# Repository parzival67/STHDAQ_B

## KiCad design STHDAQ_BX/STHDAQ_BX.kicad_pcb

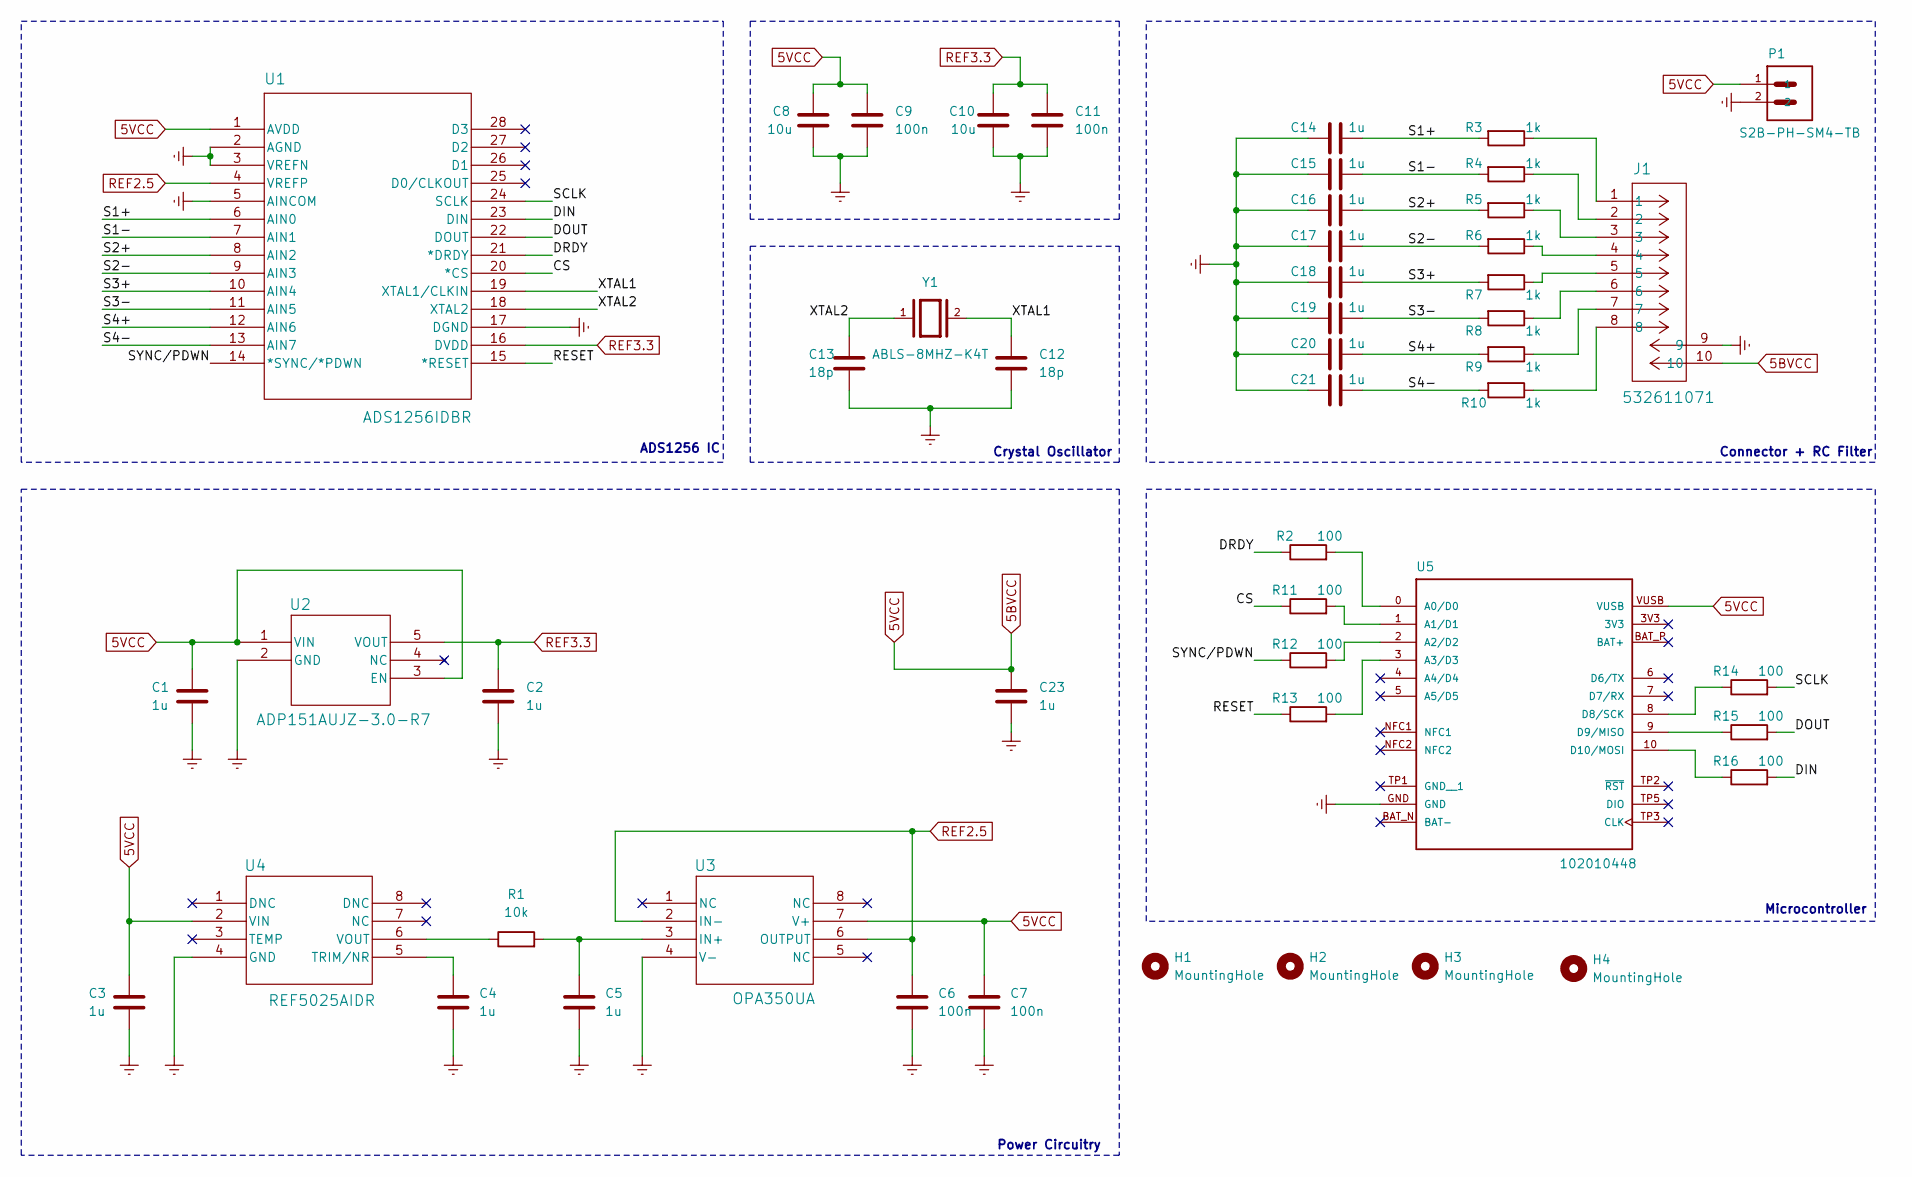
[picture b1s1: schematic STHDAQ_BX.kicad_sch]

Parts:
C1, C2, C3, C4, C5, C14, C15, C16, C17, C18, C19, C20, C21, C23: 1u; C_0603_1608Metric_Pad1.08x0.95mm_HandSolder
C6, C7, C9, C11: 100n; C_0603_1608Metric_Pad1.08x0.95mm_HandSolder
C8, C10: 10u; C_0603_1608Metric_Pad1.08x0.95mm_HandSolder
C12, C13: 18p; C_0603_1608Metric_Pad1.08x0.95mm_HandSolder
H1, H2, H3, H4: MountingHole; MountingHole_3.2mm_M3_ISO14580_Pad_TopBottom
J1: 532611071; CONN_532610001
P1: S2B-PH-SM4-TB; JST_S2B-PH-SM4-TB
R1: 10k; R_0603_1608Metric_Pad0.98x0.95mm_HandSolder
R2, R11, R12, R13, R14, R15, R16: 100; R_0603_1608Metric_Pad0.98x0.95mm_HandSolder
R3, R4, R5, R6, R7, R8, R9, R10: 1k; R_0603_1608Metric_Pad0.98x0.95mm_HandSolder
U1: ADS1256IDBR
U2: ADP151AUJZ-3.0-R7; ADP151AUJZ-3P0-R7
U3: OPA350UA
U4: REF5025AIDR
U5: 102010448; PARTREV 2022/08/18
Y1: ABLS-8MHZ-K4T; XTAL_ABLS-8.000MHZ-K4T; PARTREV 02.16.2021

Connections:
5BVCC: C1.2, C3.2, C7.2, C8.2, C9.2, C23.2, J1.10, P1.1, U1.1 (AVDD), U2.1 (VIN), U2.3 (EN), U3.7 (V+), U4.2 (VIN), U5.VUSB
/CS: R11.1, U1.20 (*CS)
/DIN: R16.2, U1.23 (DIN)
/DOUT: R15.2, U1.22 (DOUT)
/DRDY: R2.1, U1.21 (*DRDY)
/RESET: R13.1, U1.15 (*RESET)
/S1+: C14.1, R3.2, U1.6 (AIN0)
/S1-: C15.1, R4.2, U1.7 (AIN1)
/S2+: C16.1, R5.2, U1.8 (AIN2)
/S2-: C17.1, R6.2, U1.9 (AIN3)
/S3+: C18.1, R7.2, U1.10 (AIN4)
/S3-: C19.1, R8.2, U1.11 (AIN5)
/S4+: C20.1, R9.2, U1.12 (AIN6)
/S4-: C21.1, R10.2, U1.13 (AIN7)
/SCLK: R14.2, U1.24 (SCLK)
/SYNC/PDWN: R12.1, U1.14 (*SYNC/*PDWN)
/XTAL1: C12.2, U1.19 (XTAL1/CLKIN), Y1.2
/XTAL2: C13.2, U1.18 (XTAL2), Y1.1
Earth: C1.1, C2.1, C3.1, C4.1, C5.1, C6.1, C7.1, C8.1, C9.1, C10.1, C11.1, C12.1, C13.1, C14.2, C15.2, C16.2, C17.2, C18.2, C19.2, C20.2, C21.2, C23.1, J1.9, P1.2, U1.2 (AGND), U1.3 (VREFN), U1.5 (AINCOM), U1.17 (DGND), U2.2 (GND), U3.4 (V-), U4.4 (GND), U5.GND
unnamed: J1.1, R3.1
unnamed: J1.2, R4.1
unnamed: J1.3, R5.1
unnamed: J1.4, R6.1
unnamed: J1.5, R7.1
unnamed: J1.6, R8.1
unnamed: J1.7, R9.1
unnamed: J1.8, R10.1
unnamed: C5.2, R1.2, U3.3 (IN+)
unnamed: C4.2, U4.5 (TRIM/NR)
unnamed: R1.1, U4.6 (VOUT)
unnamed: R2.2, U5.0 (A0/D0)
unnamed: R11.2, U5.1 (A1/D1)
unnamed: R12.2, U5.2 (A2/D2)
unnamed: R13.2, U5.3 (A3/D3)
unnamed: R14.1, U5.8 (D8/SCK)
unnamed: R15.1, U5.9 (D9/MISO)
unnamed: R16.1, U5.10 (D10/MOSI)
REF2.5: C6.2, U1.4 (VREFP), U3.2 (IN-), U3.6 (OUTPUT)
REF3.3: C2.2, C10.2, C11.2, U1.16 (DVDD), U2.5 (VOUT)

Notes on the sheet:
Connector + RC Filter
Microcontroller
Power Circuitry
ADS1256 IC
Crystal Oscillator

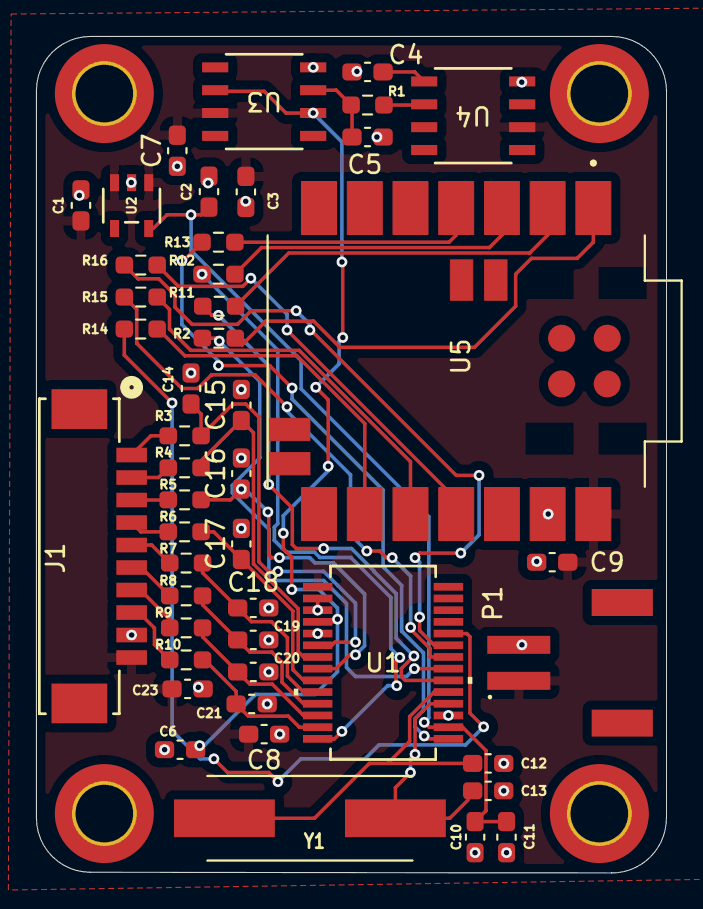
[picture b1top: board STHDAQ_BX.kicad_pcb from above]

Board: 2 copper layers, 35.0 x 46.5 mm, 50 parts (0 on the bottom side), 39 nets.

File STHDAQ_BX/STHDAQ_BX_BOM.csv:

"Reference","Qty","Value","Datasheet","Footprint","DNP","#","MANUFACTURER","Package","Description"
"P1","1","S2B-PH-SM4-TB","","daFootprintsBX:JST_S2B-PH-SM4-TB","","1","JST","None",""
"U4","1","REF5025AIDR","REF5025AIDR","daFootprints:REF5025AIDR","","2","","",""
"U3","1","OPA350UA","OPA350UA","daFootprints:OPA350UA","","3","","",""
"U1","1","ADS1256IDBR","ADS1256IDBR","daFootprints:ADS1256IDBR","","4","","",""
"U2","1","ADP151AUJZ-3.0-R7","ADP151AUJZ-3.0-R7","daFootprints:ADP151AUJZ-3P0-R7","","5","","",""
"Y1","1","ABLS-8MHZ-K4T","","daFootprints:XTAL_ABLS-8.000MHZ-K4T","","6","Abracon","HC-49/US Abracon LLC",""
"J1","1","532611071","532611071","daFootprints:CONN_532610001","","7","","",""
"U5","1","102010448","","daFootprints:102010448","","8","Seeed Technology Co., Ltd","None",""
"R1","1","10k","~","Resistor_SMD:R_0603_1608Metric_Pad0.98x0.95mm_HandSolder","","9","","","Resistor"
"R3,R4,R5,R6,R7,R8,R9,R10","8","1k","~","Resistor_SMD:R_0603_1608Metric_Pad0.98x0.95mm_HandSolder","","10","","","Resistor"
"R2,R11,R12,R13,R14,R15,R16","7","100","~","Resistor_SMD:R_0603_1608Metric_Pad0.98x0.95mm_HandSolder","","11","","","Resistor"
"C8,C10","2","10u","~","Capacitor_SMD:C_0603_1608Metric_Pad1.08x0.95mm_HandSolder","","12","","","Unpolarized capacitor"
"C1,C2,C3,C4,C5,C14,C15,C16,C17,C18,C19,C20,C21,C23","14","1u","~","Capacitor_SMD:C_0603_1608Metric_Pad1.08x0.95mm_HandSolder","","13","","","Unpolarized capacitor"
"C6,C7,C9,C11","4","100n","~","Capacitor_SMD:C_0603_1608Metric_Pad1.08x0.95mm_HandSolder","","14","","","Unpolarized capacitor"
"C12,C13","2","18p","~","Capacitor_SMD:C_0603_1608Metric_Pad1.08x0.95mm_HandSolder","","15","","","Unpolarized capacitor"

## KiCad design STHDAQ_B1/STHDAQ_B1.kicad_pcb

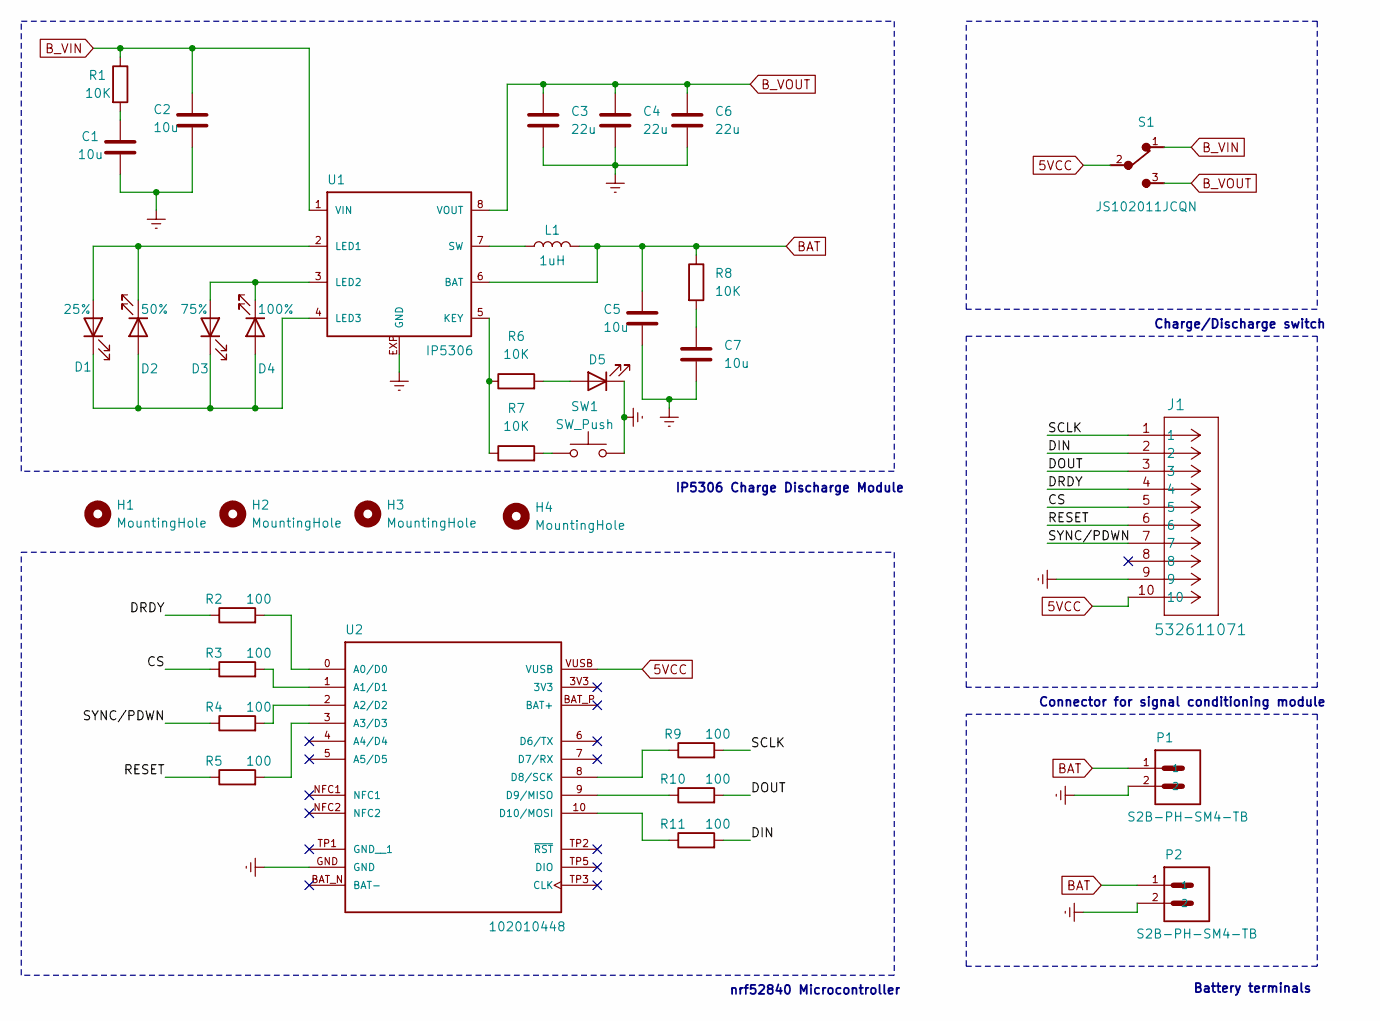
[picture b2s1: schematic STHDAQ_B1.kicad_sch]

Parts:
C1, C2, C5, C7: 10u; C_0603_1608Metric_Pad1.08x0.95mm_HandSolder
C3, C4, C6: 22u; C_0603_1608Metric_Pad1.08x0.95mm_HandSolder
D1: 25%; LED_0603_1608Metric_Pad1.05x0.95mm_HandSolder
D2: 50%; LED_0603_1608Metric_Pad1.05x0.95mm_HandSolder
D3: 75%; LED_0603_1608Metric_Pad1.05x0.95mm_HandSolder
D4: 100%; LED_0603_1608Metric_Pad1.05x0.95mm_HandSolder
D5: LED; LED_0603_1608Metric_Pad1.05x0.95mm_HandSolder
H1, H2, H3, H4: MountingHole; MountingHole_3.2mm_M3_ISO14580_Pad_TopBottom
J1: 532611071; CONN_532610001
L1: 1uH; L_0603_1608Metric_Pad1.05x0.95mm_HandSolder
P1, P2: S2B-PH-SM4-TB; JST_S2B-PH-SM4-TB
R1, R6, R7, R8: 10K; R_0603_1608Metric_Pad0.98x0.95mm_HandSolder
R2, R3, R4, R5, R9, R10, R11: 100; R_0603_1608Metric_Pad0.98x0.95mm_HandSolder
S1: JS102011JCQN; SW_JS102011JCQN; PARTREV 29 JUN 2016
SW1: SW_Push; Panasonic_EVQPUJ_EVQPUA
U1: IP5306
U2: 102010448; PARTREV 2022/08/18

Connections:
5VCC: J1.10, S1.2, U2.VUSB
/CS: J1.5, R3.1
/DIN: J1.2, R11.2
/DOUT: J1.3, R10.2
/DRDY: J1.4, R2.1
/RESET: J1.6, R5.1
/SCLK: J1.1, R9.2
/SYNC/PDWN: J1.7, R4.1
BAT: C5.1, L1.2, P1.1, P2.1, R8.1, U1.6 (BAT)
B_VIN: C2.1, R1.1, S1.1, U1.1 (VIN)
B_VOUT: C3.1, C4.1, C6.1, S1.3, U1.8 (VOUT)
Earth: C1.2, C2.2, C3.2, C4.2, C5.2, C6.2, C7.2, D5.1 (K), J1.9, P1.2, P2.2, SW1.2, U1.EXP (GND), U2.GND
unnamed: C1.1, R1.2
unnamed: C7.1, R8.2
unnamed: D1.2 (A), D2.1 (K), U1.2 (LED1)
unnamed: D1.1 (K), D2.2 (A), D3.1 (K), D4.2 (A), U1.4 (LED3)
unnamed: D3.2 (A), D4.1 (K), U1.3 (LED2)
unnamed: D5.2 (A), R6.2
unnamed: R7.2, SW1.1
unnamed: R6.1, R7.1, U1.5 (KEY)
unnamed: L1.1, U1.7 (SW)
unnamed: R2.2, U2.0 (A0/D0)
unnamed: R3.2, U2.1 (A1/D1)
unnamed: R4.2, U2.2 (A2/D2)
unnamed: R5.2, U2.3 (A3/D3)
unnamed: R9.1, U2.8 (D8/SCK)
unnamed: R10.1, U2.9 (D9/MISO)
unnamed: R11.1, U2.10 (D10/MOSI)

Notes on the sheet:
nrf52840 Microcontroller
Connector for signal conditioning module
Battery terminals
IP5306 Charge Discharge Module
Charge/Discharge switch

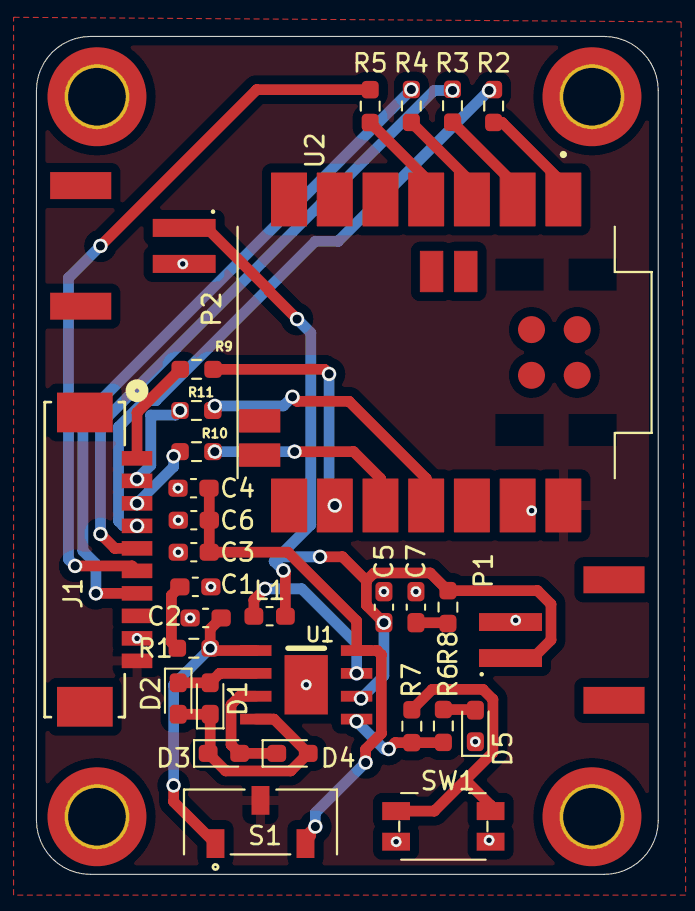
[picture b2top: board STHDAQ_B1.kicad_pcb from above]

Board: 2 copper layers, 34.5 x 46.6 mm, 35 parts (0 on the bottom side), 28 nets.

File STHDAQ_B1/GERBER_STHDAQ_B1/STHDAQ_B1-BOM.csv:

#,Reference,Qty,MANUFACTURER,Manufacturer Part Number,Value,Package,Type
1,"P1,P2",2,JST Sales America Inc.,S2B-PH-SM4-TB,-,,SMD
2,S1,1,CK COMPONENTS,JS102011JCQN,-,,SMD
3,U1,1,,IP5306,-,,SMD
4,J1,1,Molex,532611071,-,S2B-PH-SM4-TB,SMD
5,"C1,C2,C5,C7",4,,,10u,0603,SMD
6,"C3,C4,C6",3,,,22u,0603,SMD
7,D1,1,,LED,25%,0603,SMD
8,D2,1,,LED,50%,0603,SMD
9,D3,1,,LED,75%,0603,SMD
10,D4,1,,LED,100%,0603,SMD
11,D5,1,,LED,LED,0603,SMD
12,L1,1,,,1uH,0603,SMD
13,"R1,R6,R7,R8",4,,,10K,0603,SMD
14,"R2,R3,R4,R5,R9,R10,R11",7,,,100,0603,SMD
15,SW1,1,,,SW_Push,,SMD

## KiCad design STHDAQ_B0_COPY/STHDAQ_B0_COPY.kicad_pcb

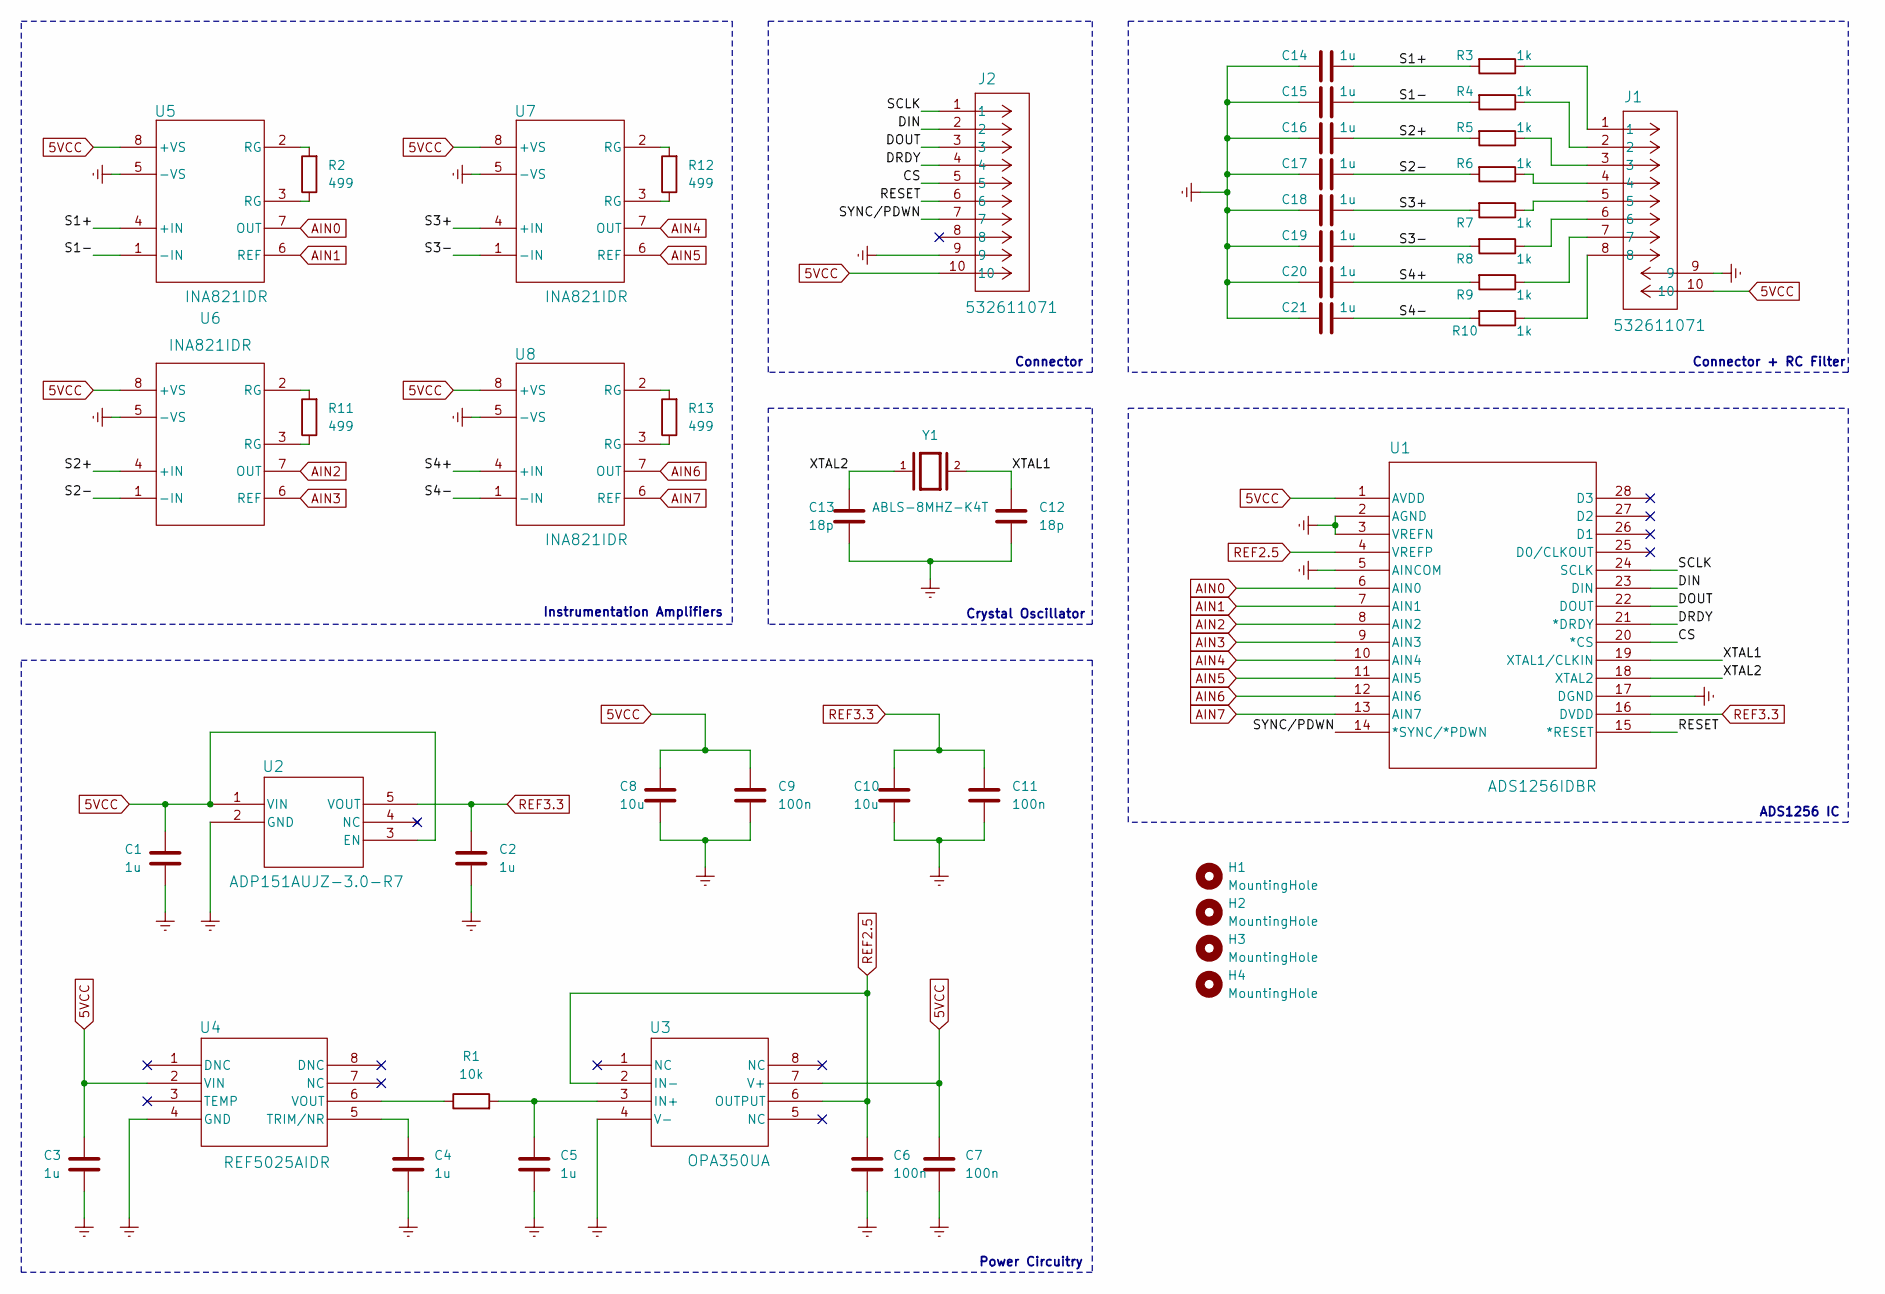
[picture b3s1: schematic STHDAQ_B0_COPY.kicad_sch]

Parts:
C1, C2, C3, C4, C5, C14, C15, C16, C17, C18, C19, C20, C21: 1u; C_0201_0603Metric
C6, C7, C9, C11: 100n; C_0201_0603Metric
C8, C10: 10u; C_0201_0603Metric
C12, C13: 18p; C_0201_0603Metric
H1, H2, H3, H4: MountingHole; MountingHole_3.2mm_M3_ISO14580_Pad_TopBottom
J1, J2: 532611071; Molex_CLIK-Mate_502382-1070_1x10-1MP_P1.25mm_Vertical
R1: 10k; R_0201_0603Metric
R2, R11, R12, R13: 499; R_0201_0603Metric
R3, R4, R5, R6, R7, R8, R9, R10: 1k; R_0201_0603Metric
U1: ADS1256IDBR
U2: ADP151AUJZ-3.0-R7; ADP151AUJZ-3P0-R7
U3: OPA350UA
U4: REF5025AIDR
U5, U6, U7, U8: INA821IDR
Y1: ABLS-8MHZ-K4T; XTAL_ABLS-8.000MHZ-K4T; PARTREV 02.16.2021

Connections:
5VCC: C1.2, C3.2, C7.2, C8.2, C9.2, J1.10, J2.10, U1.1 (AVDD), U2.1 (VIN), U2.3 (EN), U3.7 (V+), U4.2 (VIN), U5.8 (+VS), U6.8 (+VS), U7.8 (+VS), U8.8 (+VS)
/CS: J2.5, U1.20 (*CS)
/DIN: J2.2, U1.23 (DIN)
/DOUT: J2.3, U1.22 (DOUT)
/DRDY: J2.4, U1.21 (*DRDY)
/RESET: J2.6, U1.15 (*RESET)
/S1+: C14.1, R3.2, U5.4 (+IN)
/S1-: C15.1, R4.2, U5.1 (-IN)
/S2+: C16.1, R5.2, U6.4 (+IN)
/S2-: C17.1, R6.2, U6.1 (-IN)
/S3+: C18.1, R7.2, U7.4 (+IN)
/S3-: C19.1, R8.2, U7.1 (-IN)
/S4+: C20.1, R9.2, U8.4 (+IN)
/S4-: C21.1, R10.2, U8.1 (-IN)
/SCLK: J2.1, U1.24 (SCLK)
/SYNC/PDWN: J2.7, U1.14 (*SYNC/*PDWN)
/XTAL1: C12.2, U1.19 (XTAL1/CLKIN), Y1.2
/XTAL2: C13.2, U1.18 (XTAL2), Y1.1
AIN0: U1.6 (AIN0), U5.7 (OUT)
AIN1: U1.7 (AIN1), U5.6 (REF)
AIN2: U1.8 (AIN2), U6.7 (OUT)
AIN3: U1.9 (AIN3), U6.6 (REF)
AIN4: U1.10 (AIN4), U7.7 (OUT)
AIN5: U1.11 (AIN5), U7.6 (REF)
AIN6: U1.12 (AIN6), U8.7 (OUT)
AIN7: U1.13 (AIN7), U8.6 (REF)
Earth: C1.1, C2.1, C3.1, C4.1, C5.1, C6.1, C7.1, C8.1, C9.1, C10.1, C11.1, C12.1, C13.1, C14.2, C15.2, C16.2, C17.2, C18.2, C19.2, C20.2, C21.2, J1.9, J2.9, U1.2 (AGND), U1.3 (VREFN), U1.5 (AINCOM), U1.17 (DGND), U2.2 (GND), U3.4 (V-), U4.4 (GND), U5.5 (-VS), U6.5 (-VS), U7.5 (-VS), U8.5 (-VS)
unnamed: J1.1, R3.1
unnamed: J1.2, R4.1
unnamed: J1.3, R5.1
unnamed: J1.4, R6.1
unnamed: J1.5, R7.1
unnamed: J1.6, R8.1
unnamed: J1.7, R9.1
unnamed: J1.8, R10.1
unnamed: R2.1, U5.3 (RG)
unnamed: R2.2, U5.2 (RG)
unnamed: R11.1, U6.3 (RG)
unnamed: R11.2, U6.2 (RG)
unnamed: R12.1, U7.3 (RG)
unnamed: R12.2, U7.2 (RG)
unnamed: R13.1, U8.3 (RG)
unnamed: R13.2, U8.2 (RG)
unnamed: C5.2, R1.2, U3.3 (IN+)
unnamed: C4.2, U4.5 (TRIM/NR)
unnamed: R1.1, U4.6 (VOUT)
REF2.5: C6.2, U1.4 (VREFP), U3.2 (IN-), U3.6 (OUTPUT)
REF3.3: C2.2, C10.2, C11.2, U1.16 (DVDD), U2.5 (VOUT)

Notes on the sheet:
Instrumentation Amplifiers
Connector + RC Filter
Connector
Power Circuitry
ADS1256 IC
Crystal Oscillator

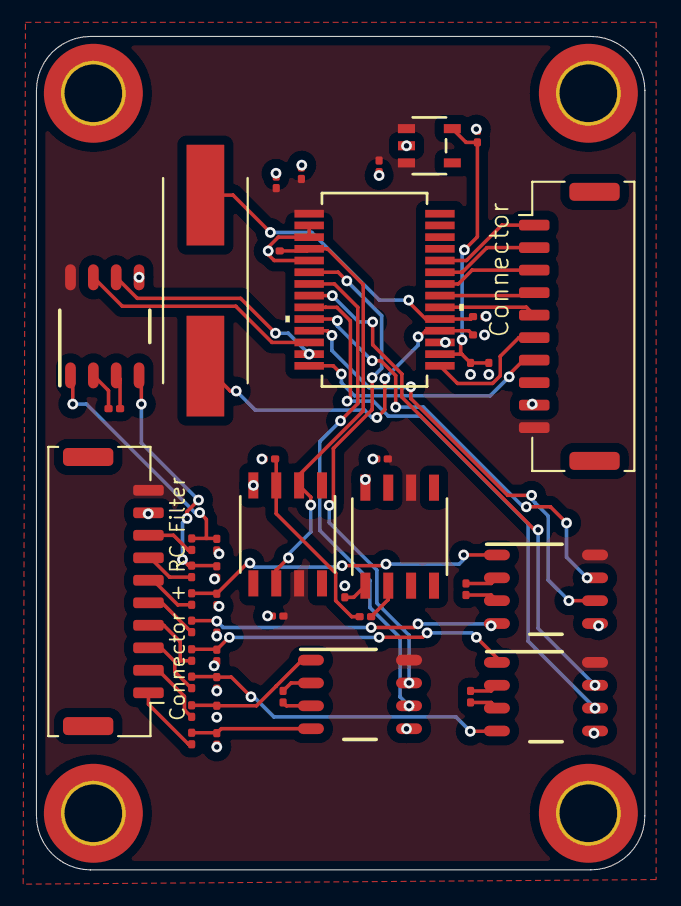
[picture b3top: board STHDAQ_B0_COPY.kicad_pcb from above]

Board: 2 copper layers, 33.8 x 46.3 mm, 49 parts (0 on the bottom side), 48 nets.

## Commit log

2024-12-21 added libraries
2024-12-21 BO schematic partially (~70%) completed
2024-12-23 started B1 schematic
2024-12-28 B1 schematic ~80% completion
2024-12-28 B1 ecad files
2025-01-08 prettify B1
2025-01-09 added resistance values for B0
2025-01-09 B0 pcb layouting ~80% completion
2025-01-09 added BX schematics and started with layout design
2025-01-10 B0 pcb layouting
2025-01-13 BX pcb layouting
2025-01-15 B1 pcb layouting
2025-03-04 Changes in BX
2025-04-02 B1 New
2025-04-15 BX New
